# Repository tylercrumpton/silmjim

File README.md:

# slimjim

**slimjim** is a multi-purpose adapter board for RF-Engine form-factor Synapse Wireless SNAP modules like the RF100 and RF200.
It also supports both versions of a custom board I've dubbed the TC200. All pins are broken out to a set of standard 0.1" 
(2.54 mm) headers for jumper cables, breadboarding, or soldering.

## Features
**slimjim** contains a few features that make using RF-Engine-style SNAP devices in one-off projects easier:

- 0.1" (2.54 mm) pin header breakout for all pins
- Silkscreen marks for pins
- Optionally-populated reset push-button
- Module orientation markers for both types of supported module

## Supported boards
The following boards should work in the **slimjim**:

- RF100/RF200/RF220 (or any other 24-pin through-hole SNAP module)
- TC200 (pin headers or USB connector)

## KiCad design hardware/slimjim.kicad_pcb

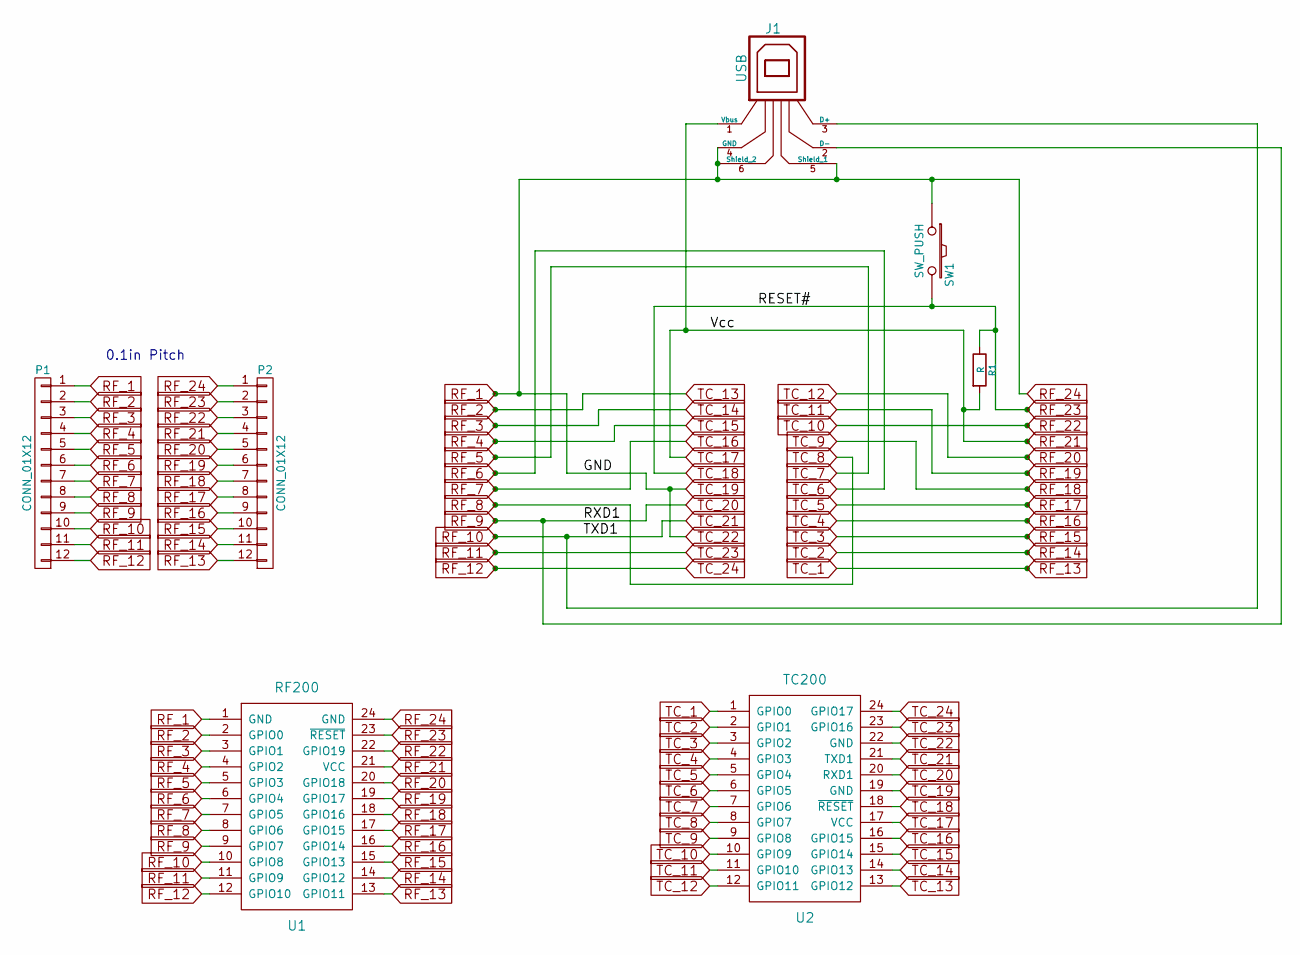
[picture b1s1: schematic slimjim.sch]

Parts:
J1: USB; USB_A
P1, P2: CONN_01X12; Header_1x12_100
R1: R; R_0805_HandSoldering
SW1: SW_PUSH; 6x6mm_pushbutton
U1: RF200; RF200_nosilk
U2: TC200; TC200_nosilk

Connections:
RF_1: J1.4 (GND), J1.5 (Shield_1), J1.6 (Shield_2), P1.1, P2.1, SW1.1, U1.1 (GND), U1.24 (GND), U2.19 (GND), U2.22 (GND)
RF_2: P1.2, U1.2 (GPIO0), U2.13 (GPIO12)
RF_3: P1.3, U1.3 (GPIO1), U2.14 (GPIO13)
RF_4: P1.4, U1.4 (GPIO2), U2.15 (GPIO14)
RF_5: P1.5, U1.5 (GPIO3), U2.7 (GPIO6)
RF_6: P1.6, U1.6 (GPIO4), U2.6 (GPIO5)
RF_7: P1.7, U1.7 (GPIO5), U2.16 (GPIO15)
RF_8: P1.8, U1.8 (GPIO6), U2.8 (GPIO7)
RF_9: J1.2 (D-), P1.9, U1.9 (GPIO7), U2.20 (RXD1)
RF_10: J1.3 (D+), P1.10, U1.10 (GPIO8), U2.21 (TXD1)
RF_11: P1.11, U1.11 (GPIO9), U2.23 (GPIO16)
RF_12: P1.12, U1.12 (GPIO10), U2.24 (GPIO17)
RF_13: P2.12, U1.13 (GPIO11), U2.1 (GPIO0)
RF_14: P2.11, U1.14 (GPIO12), U2.2 (GPIO1)
RF_15: P2.10, U1.15 (GPIO13), U2.3 (GPIO2)
RF_16: P2.9, U1.16 (GPIO14), U2.4 (GPIO3)
RF_17: P2.8, U1.17 (GPIO15), U2.5 (GPIO4)
RF_18: P2.7, U1.18 (GPIO16), U2.9 (GPIO8)
RF_19: P2.6, U1.19 (GPIO17), U2.11 (GPIO10)
RF_20: P2.5, U1.20 (GPIO18), U2.12 (GPIO11)
RF_21: J1.1 (Vbus), P2.4, R1.2, U1.21 (VCC), U2.17 (VCC)
RF_22: P2.3, U1.22 (GPIO19), U2.10 (GPIO9)
RF_23: P2.2, R1.1, SW1.2, U1.23 (~RESET), U2.18 (~RESET)

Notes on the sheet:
0.1in Pitch

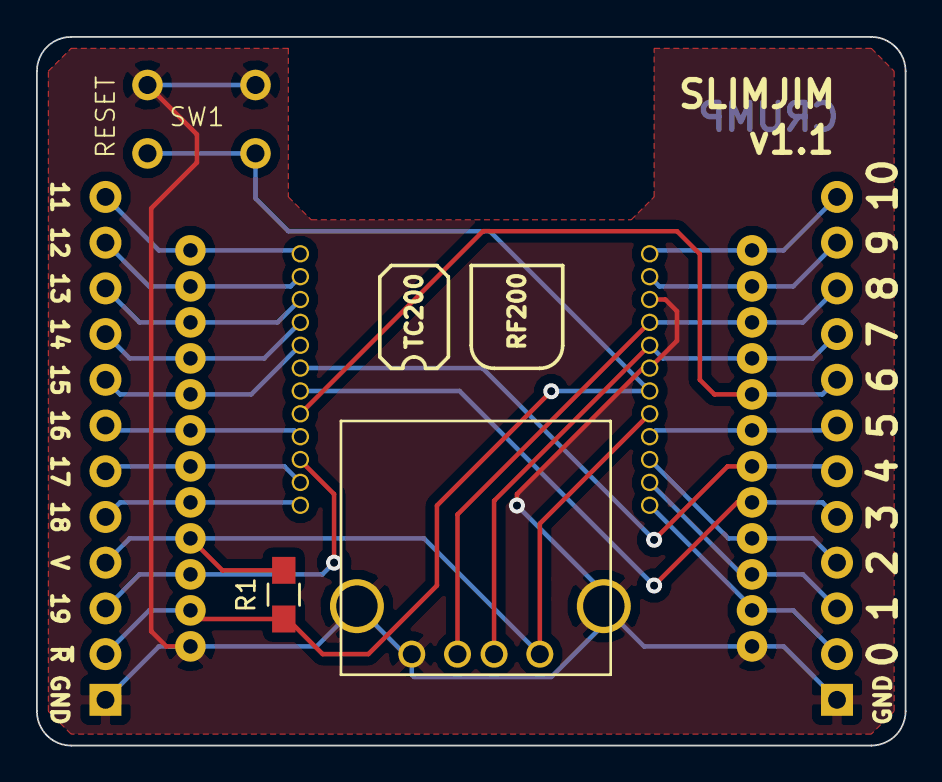
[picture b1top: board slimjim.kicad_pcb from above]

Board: 2 copper layers, 48.3 x 39.4 mm, 7 parts (0 on the bottom side), 23 nets.

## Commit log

2016-03-24 Initial schematic capture.
2016-04-01 Replace generic pin headers with actual parts.
2016-04-02 Make tiny tweak to a wire in schematic.
2016-04-02 Update red to CrumpPrints to get new pin header.
2016-04-02 Initial part placement.
2016-04-02 Improve part placement.
2016-04-02 Initial routing.
2016-04-02 PCB cleanup.
2016-04-02 Setup gerber plotting.
2016-05-10 Add dirty recover script for TC200s.
2016-05-13 Update recover script to change nvparams.
2016-09-12 Refresh project.
2016-09-12 Widen board and add pin silkscreens.
2016-09-12 Clean up silkscreens for RF200 and TC200.
2016-09-12 Add README.
2016-09-12 Fix typo in README.

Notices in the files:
hardware/slimjim.kicad_pcb:
CC-BY-SA 4.0
